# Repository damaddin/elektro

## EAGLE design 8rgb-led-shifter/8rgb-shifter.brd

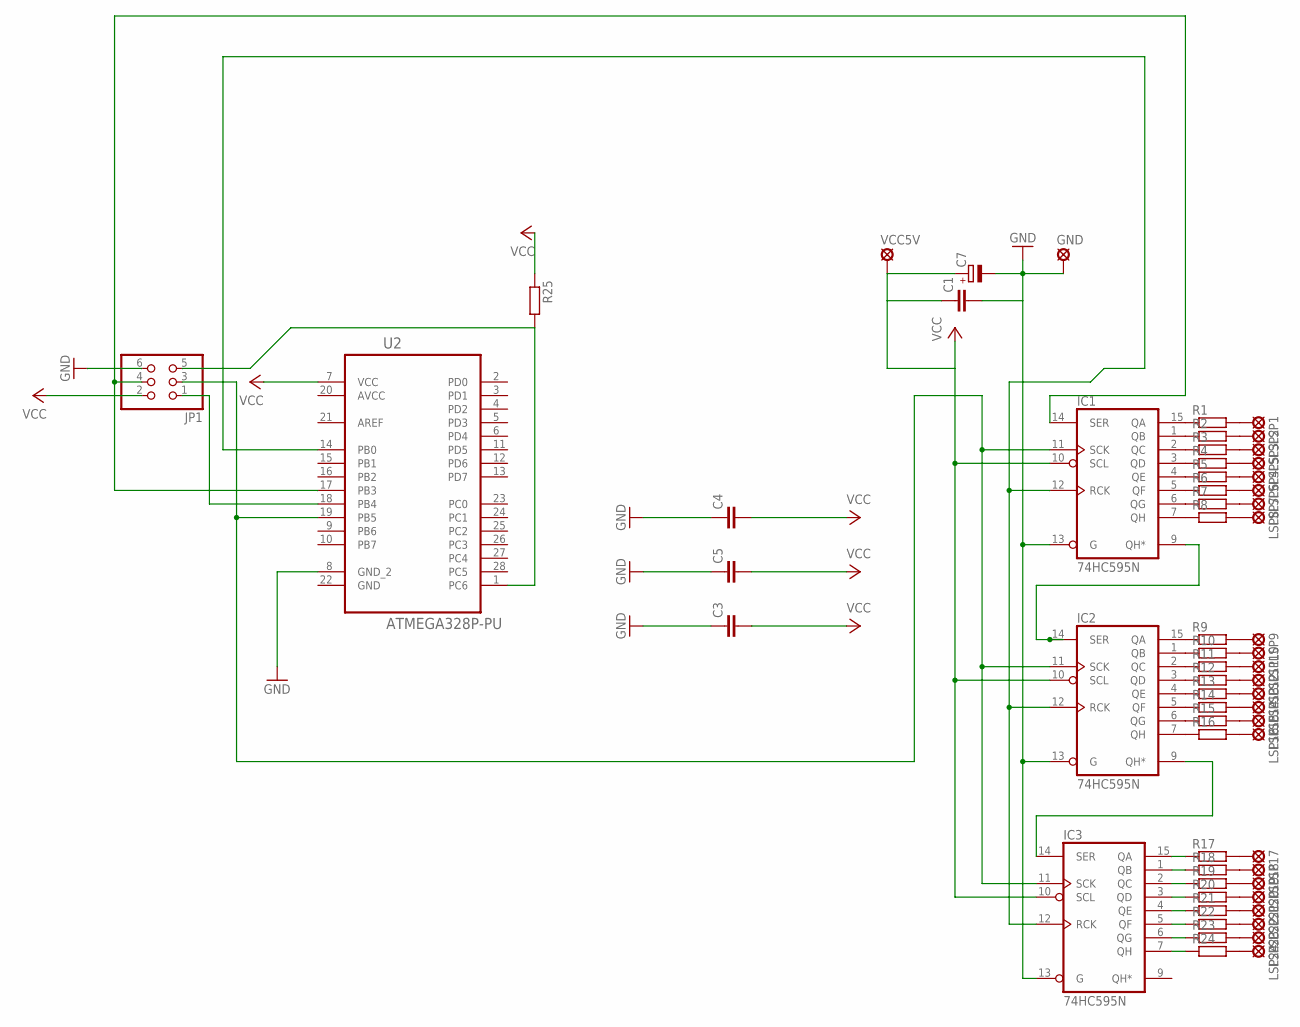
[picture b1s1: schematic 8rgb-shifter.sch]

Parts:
C1, C3, C4, C5: C-EU025-025X050; C025-025X050
C7: CPOL-EUE2,5-6E; E2,5-6E
GND: LSP10
IC1, IC2, IC3: 74HC595N; DIL16
JP1: PINHD-2X3; 2X03
LSP1, LSP2, LSP3, LSP4, LSP5, LSP6, LSP7, LSP8, LSP9, LSP10, LSP11, LSP12, LSP13, LSP14, LSP15, LSP16, LSP17, LSP18, LSP19, LSP20, LSP21, LSP22, LSP23, LSP24: LSP10
R1, R2, R3, R4, R5, R6, R7, R8, R9, R10, R11, R12, R13, R14, R15, R16, R17, R18, R19, R20, R21, R22, R23, R24: R-EU_0204/2V; 0204V
R25: R-EU_0204/7; 0204/7
U2: ATMEGA328P-PU; DIP254P762X457-28
VCC5V: LSP10

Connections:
AVCC: U2.20 (AVCC)
GND: C4.1, JP1.6, U2.8 (GND_2)
unnamed: JP1.1, U2.18 (PB4)
unnamed: IC1.11 (SCK), IC2.11 (SCK), IC3.11 (SCK), JP1.3, U2.19 (PB5)
unnamed: LSP1.MP, R1.2
unnamed: IC1.9 (QH*), IC2.14 (SER)
unnamed: IC2.9 (QH*), IC3.14 (SER)
unnamed: LSP17.MP, R17.2
unnamed: JP1.5, R25.2, U2.1 (PC6)
unnamed: IC1.14 (SER), JP1.4, U2.17 (PB3)
unnamed: IC1.15 (QA), R1.1
unnamed: IC1.1 (QB), R2.1
unnamed: IC1.2 (QC), R3.1
unnamed: IC1.3 (QD), R4.1
unnamed: IC1.4 (QE), R5.1
unnamed: IC1.5 (QF), R6.1
unnamed: IC1.6 (QG), R7.1
unnamed: IC1.7 (QH), R8.1
unnamed: IC2.15 (QA), R9.1
unnamed: IC2.1 (QB), R10.1
unnamed: IC2.2 (QC), R11.1
unnamed: IC2.3 (QD), R12.1
unnamed: IC2.4 (QE), R13.1
unnamed: IC2.5 (QF), R14.1
unnamed: IC2.6 (QG), R15.1
unnamed: IC2.7 (QH), R16.1
unnamed: IC3.15 (QA), R17.1
unnamed: IC3.1 (QB), R18.1
unnamed: IC3.2 (QC), R19.1
unnamed: IC3.3 (QD), R20.1
unnamed: IC3.4 (QE), R21.1
unnamed: IC3.5 (QF), R22.1
unnamed: IC3.6 (QG), R23.1
unnamed: IC3.7 (QH), R24.1
unnamed: LSP2.MP, R2.2
unnamed: LSP3.MP, R3.2
unnamed: LSP4.MP, R5.2
unnamed: LSP5.MP, R4.2
unnamed: LSP6.MP, R6.2
unnamed: LSP7.MP, R7.2
unnamed: LSP8.MP, R8.2
unnamed: LSP9.MP, R9.2
unnamed: LSP10.MP, R10.2
unnamed: LSP12.MP, R12.2
unnamed: LSP13.MP, R13.2
unnamed: LSP14.MP, R14.2
unnamed: LSP15.MP, R15.2
unnamed: LSP11.MP, R11.2
unnamed: LSP16.MP, R16.2
unnamed: LSP18.MP, R18.2
unnamed: LSP19.MP, R19.2
unnamed: LSP20.MP, R20.2
unnamed: LSP21.MP, R21.2
unnamed: LSP23.MP, R23.2
unnamed: LSP24.MP, R24.2
unnamed: LSP22.MP, R22.2
unnamed: C1.2, C3.1, C5.1, C7.-, GND.MP, IC1.8 (GND), IC1.13 (G), IC2.8 (GND), IC2.13 (G), IC3.8 (GND), IC3.13 (G)
unnamed: IC1.12 (RCK), IC2.12 (RCK), IC3.12 (RCK), U2.14 (PB0)
VCC: C1.1, C3.2, C4.2, C5.2, C7.+, IC1.10 (SCL), IC1.16 (VCC), IC2.10 (SCL), IC2.16 (VCC), IC3.10 (SCL), IC3.16 (VCC), JP1.2, R25.1, U2.7 (VCC), VCC5V.MP

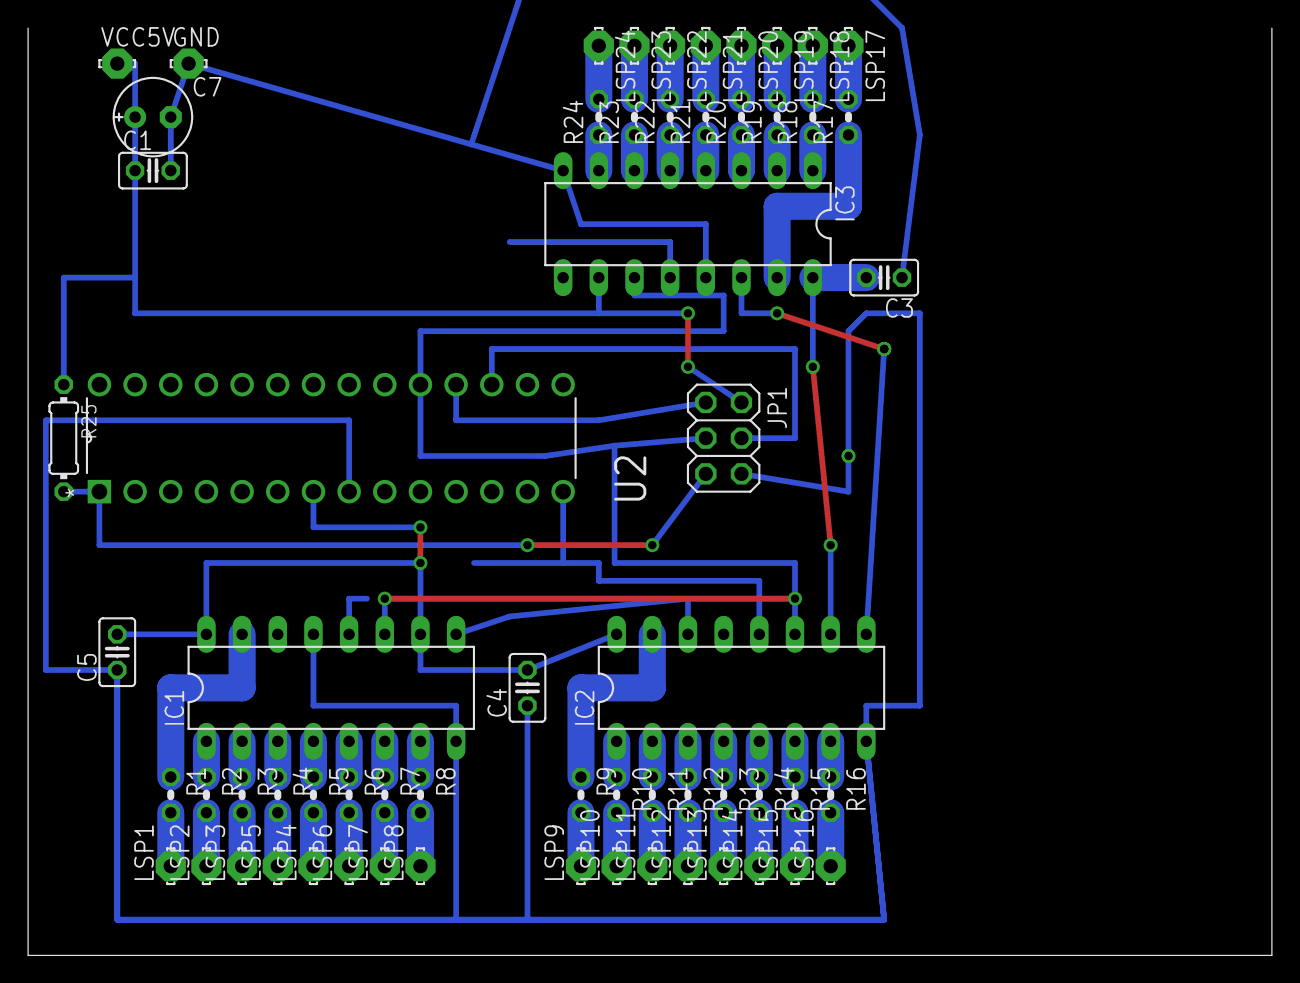
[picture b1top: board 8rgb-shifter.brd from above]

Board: 2 copper layers, 88.6 x 66.0 mm, 61 parts (0 on the bottom side), 58 nets.

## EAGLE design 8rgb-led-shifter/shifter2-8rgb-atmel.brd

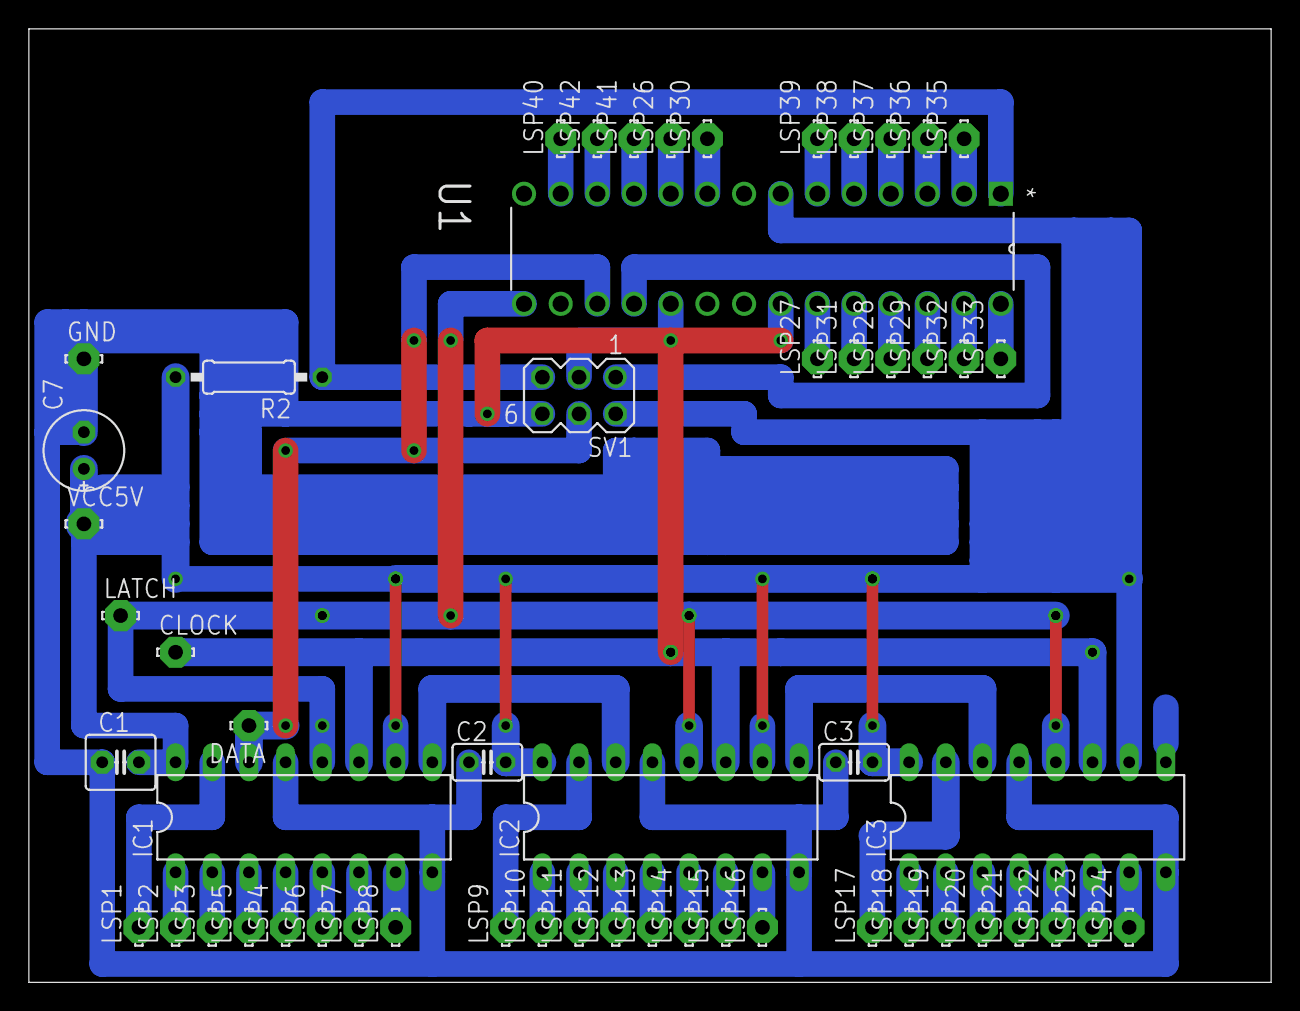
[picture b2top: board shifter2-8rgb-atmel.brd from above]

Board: 2 copper layers, 86.0 x 66.0 mm, 55 parts (0 on the bottom side), 50 nets.

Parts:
C1: C2.5-4
C2, C3: C025-025X050
C7: E2,5-6E
CLOCK: LSP10
DATA: LSP10
GND: LSP10
IC1, IC2, IC3: 74HC595N; DIL16
LATCH: LSP10
LSP1, LSP2, LSP3, LSP4, LSP5, LSP6, LSP7, LSP8, LSP9, LSP10, LSP11, LSP12, LSP13, LSP14, LSP15, LSP16, LSP17, LSP18, LSP19, LSP20, LSP21, LSP22, LSP23, LSP24, LSP26, LSP27, LSP28, LSP29, LSP30, LSP31, LSP32, LSP33, LSP35, LSP36, LSP37, LSP38, LSP39, LSP40, LSP41, LSP42: LSP10
R2: 0207/10
SV1: MA03-2
U1: ATMEGA168A-PU; DIP254P762X457-28
VCC5V: LSP10

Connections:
GND: SV1.6, U1.22
unnamed: IC2.15, LSP9.MP
unnamed: IC2.1, LSP10.MP
unnamed: IC2.2, LSP11.MP
unnamed: IC1.9, IC2.14
unnamed: IC2.9, IC3.14
unnamed: IC2.3, LSP12.MP
unnamed: IC2.4, LSP13.MP
unnamed: IC2.5, LSP14.MP
unnamed: IC2.6, LSP15.MP
unnamed: IC2.7, LSP16.MP
unnamed: IC1.15, LSP1.MP
unnamed: IC1.1, LSP2.MP
unnamed: IC1.2, LSP3.MP
unnamed: IC1.4, LSP4.MP
unnamed: IC1.3, LSP5.MP
unnamed: IC1.5, LSP6.MP
unnamed: IC1.6, LSP7.MP
unnamed: IC1.7, LSP8.MP
unnamed: R2.1, SV1.5, U1.1
unnamed: LSP28.MP, U1.25
unnamed: DATA.MP, IC1.14, SV1.4, U1.17
unnamed: SV1.1, U1.18
unnamed: LSP29.MP, U1.26
unnamed: LSP26.MP, U1.10
unnamed: LSP30.MP, U1.9
unnamed: IC3.15, LSP17.MP
unnamed: IC3.1, LSP18.MP
unnamed: IC3.2, LSP19.MP
unnamed: IC3.3, LSP20.MP
unnamed: IC3.4, LSP21.MP
unnamed: IC3.5, LSP22.MP
unnamed: IC3.6, LSP23.MP
unnamed: IC3.7, LSP24.MP
unnamed: LSP27.MP, U1.23
unnamed: LSP31.MP, U1.24
unnamed: LSP32.MP, U1.27
unnamed: LSP33.MP, U1.28
unnamed: LSP35.MP, U1.2
unnamed: LSP36.MP, U1.3
unnamed: LSP37.MP, U1.4
unnamed: LSP38.MP, U1.5
unnamed: LSP39.MP, U1.6
unnamed: LSP41.MP, U1.11
unnamed: LSP42.MP, U1.12
unnamed: LSP40.MP, U1.13
unnamed: CLOCK.MP, IC1.11, IC2.11, IC3.11, SV1.3, U1.19
unnamed: C1.1, C2.1, C3.1, C7.-, GND.MP, IC1.8, IC1.13, IC2.8, IC2.13, IC3.8, IC3.13
unnamed: IC1.12, IC2.12, IC3.12, LATCH.MP, U1.15
VCC: C1.2, C2.2, C3.2, C7.+, IC1.10, IC1.16, IC2.10, IC2.16, IC3.10, IC3.16, R2.2, SV1.2, U1.7, VCC5V.MP

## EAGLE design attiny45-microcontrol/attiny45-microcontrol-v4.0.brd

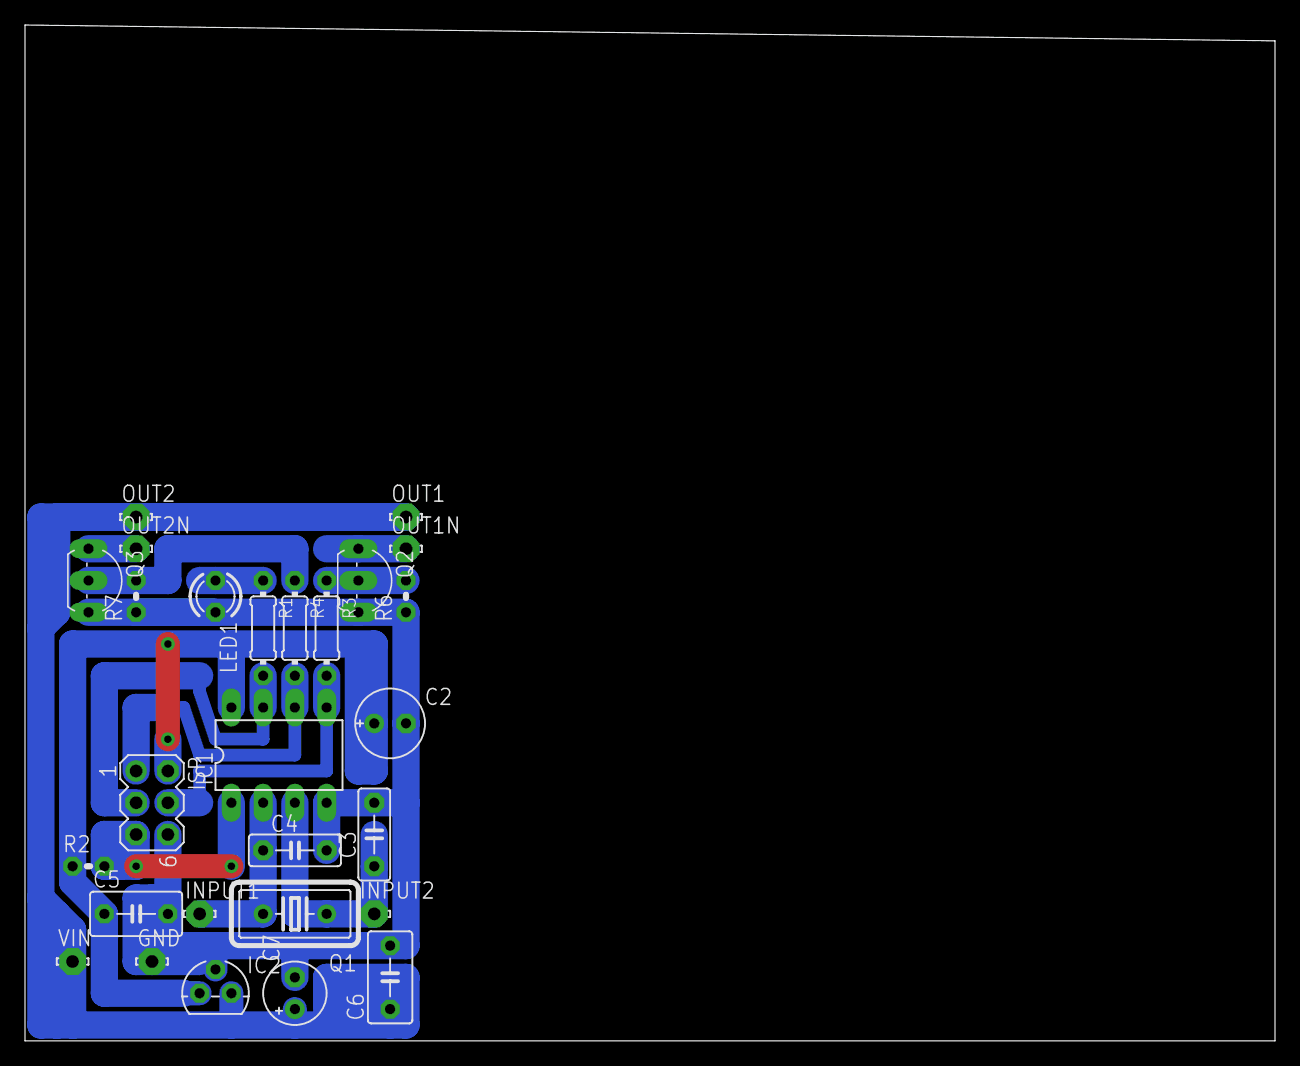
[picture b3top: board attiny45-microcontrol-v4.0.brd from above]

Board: 2 copper layers, 100.0 x 81.3 mm, 27 parts (0 on the bottom side), 14 nets.

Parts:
C2: 100u; E2,5-6E
C3, C4: 18nf; C5B2.5
C5, C6: 100n; C050-035X075
C7: 100y; E2,5-5
GND: LSP10
IC1: ATtiny13V; DIL08
IC2: 7805L; TO92
INPUT1, INPUT2: LSP10
ISP: isp 1; MA03-2
LED1: ROT; LED3MM
OUT1, OUT1N, OUT2, OUT2N: LSP10
Q1: 8mhz; HC18U-V
Q2, Q3: BC548; TO92-EBC
R1: 390; 0204/7
R2, R6, R7: 10k; 0204V
R3, R4: 1k; 0204/7
VIN: LSP10

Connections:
GND: C2.-, C3.2, C4.2, C5.2, C6.2, C7.-, GND.MP, IC1.4, IC2.2, ISP.6, LED1.K, Q2.E, Q3.E, R6.1, R7.1
unnamed: Q2.B, R3.1, R6.2
unnamed: C4.1, IC1.2, INPUT1.MP, Q1.2
unnamed: IC1.1, ISP.5, R2.2
unnamed: Q3.B, R4.1, R7.2
unnamed: IC1.7, ISP.3, R1.2
unnamed: IC1.6, ISP.1, R4.2
unnamed: LED1.A, R1.1
unnamed: C3.1, IC1.3, INPUT2.MP, Q1.1
unnamed: IC1.5, ISP.4, R3.2
unnamed: OUT2N.MP, Q3.C
unnamed: OUT1N.MP, Q2.C
unnamed: C6.1, C7.+, IC2.3, OUT1.MP, OUT2.MP, VIN.MP
VCC: C2.+, C5.1, IC1.8, IC2.1, ISP.2, R2.1

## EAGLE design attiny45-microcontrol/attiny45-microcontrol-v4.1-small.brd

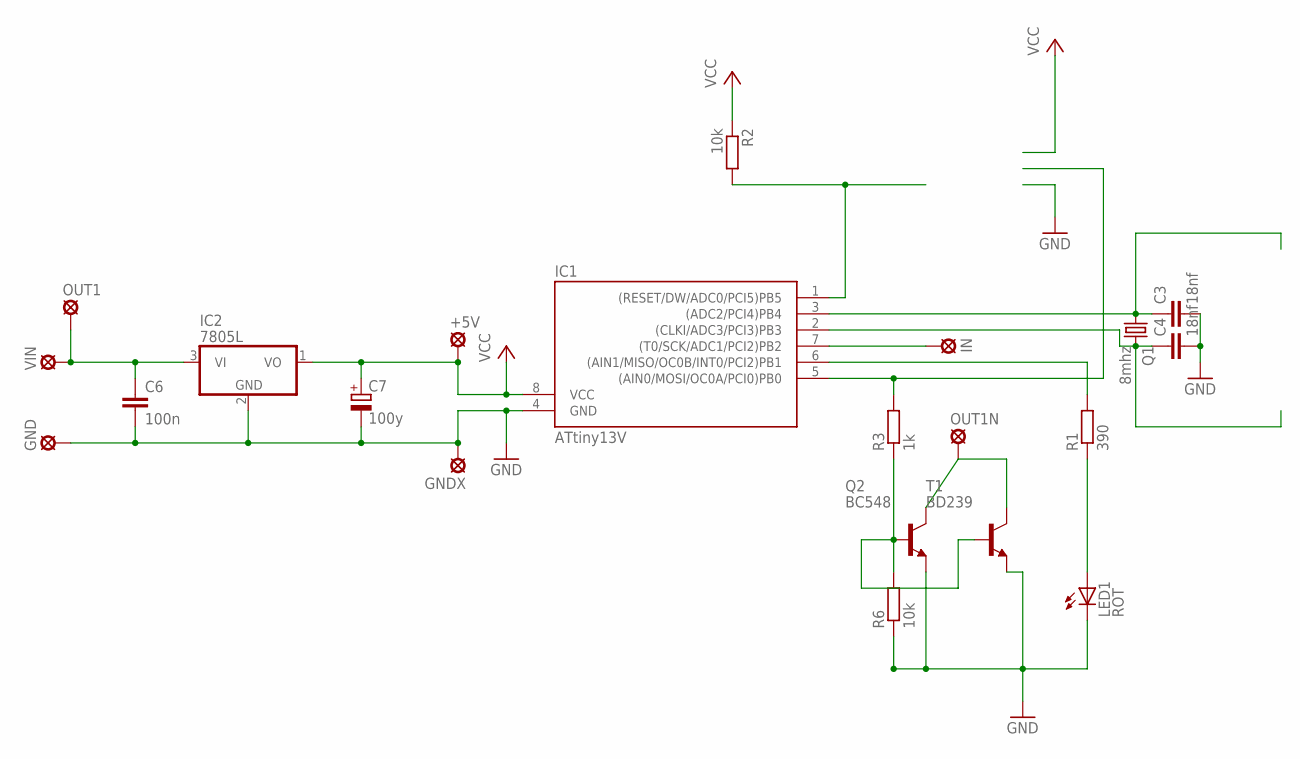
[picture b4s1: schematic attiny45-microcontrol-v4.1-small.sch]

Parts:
+5V: LSP10
C3, C4: 18nf; C5B2.5
C6: 100n; C050-035X075
C7: 100y; E2,5-5
GND: LSP10
GNDX: LSP10
IC1: ATtiny13V; DIL08
IC2: 7805L; TO92
IN: LSP10
LED1: ROT; LED3MM
OUT1, OUT1N: LSP10
Q1: 8mhz; HC18U-V
Q2: BC548; TO92-EBC
R1: 390; 0204/7
R2, R6: 10k; R1206
R3: 1k; 0204/7
T1: BD239; TO220
VIN: LSP10

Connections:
GND: C3.2, C4.2, C6.2, C7.-, GND.MP, GNDX.MP, IC1.4 (GND), IC2.2 (GND), LED1.K (C), Q2.E, R6.1, T1.3 (E)
unnamed: Q2.B, R3.1, R6.2, T1.1 (B)
unnamed: C4.1, IC1.2 ((CLKI/ADC3/PCI3)PB3), Q1.2
unnamed: IC1.1 ((RESET/DW/ADC0/PCI5)PB5), R2.2
unnamed: IC1.7 ((T0/SCK/ADC1/PCI2)PB2), IN.MP
unnamed: IC1.6 ((AIN1/MISO/OC0B/INT0/PCI2)PB1), R1.2
unnamed: LED1.A, R1.1
unnamed: C3.1, IC1.3 ((ADC2/PCI4)PB4), Q1.1
unnamed: IC1.5 ((AIN0/MOSI/OC0A/PCI0)PB0), R3.2
unnamed: OUT1N.MP, Q2.C, T1.2 (C)
unnamed: C6.1, IC2.3 (VI), OUT1.MP, VIN.MP
VCC: +5V.MP, C7.+, IC1.8 (VCC), IC2.1 (VO), R2.1

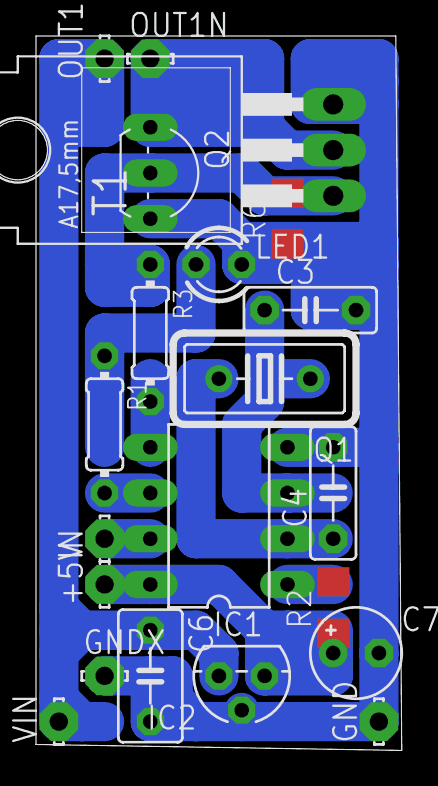
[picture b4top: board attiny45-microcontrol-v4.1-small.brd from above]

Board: 2 copper layers, 20.3 x 39.7 mm, 21 parts (0 on the bottom side), 12 nets.

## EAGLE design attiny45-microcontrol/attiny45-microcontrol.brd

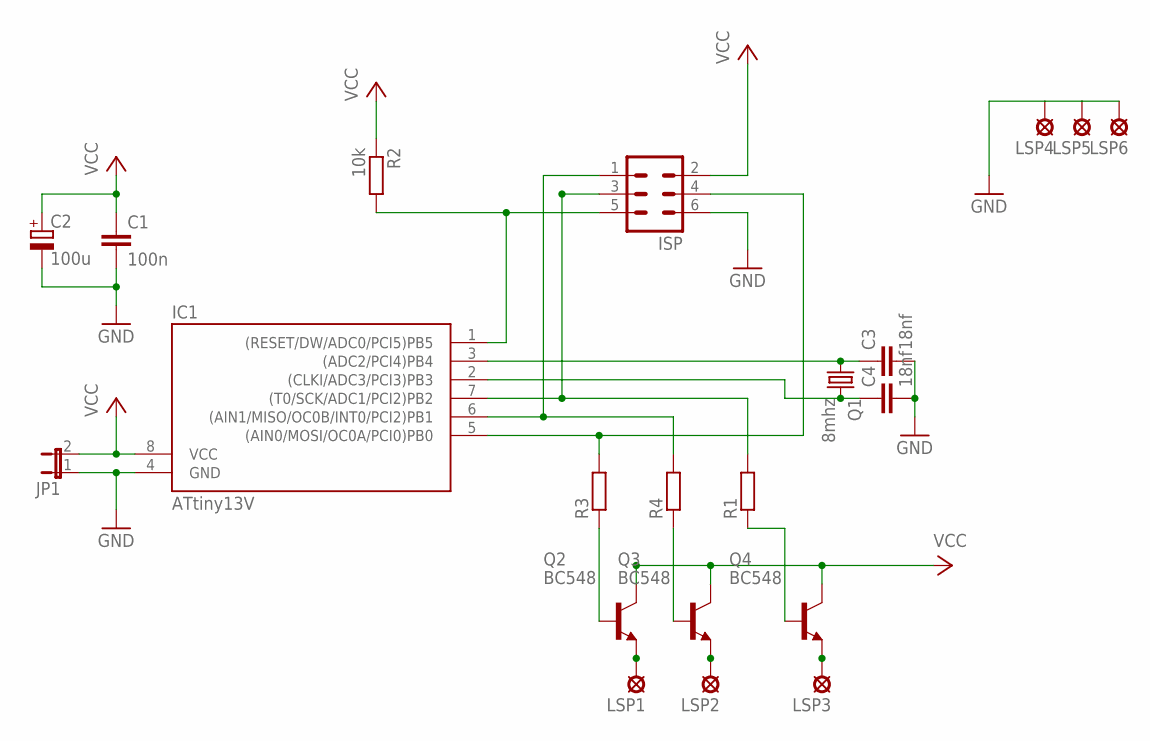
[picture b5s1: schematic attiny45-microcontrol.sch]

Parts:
C1: 100n; C025-025X050
C2: 100u; E2,5-6E
C3, C4: 18nf; C5B2.5
IC1: ATtiny13V; DIL08
ISP: MA03-2
JP1: JP1E; JP1
LSP1, LSP2, LSP3, LSP4, LSP5, LSP6: LSP10
Q1: 8mhz; HC18U-V
Q2, Q3, Q4: BC548; TO92-EBC
R1, R3, R4: R-EU_0204/5; 0204/5
R2: 10k; 0204/7

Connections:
GND: C1.2, C2.-, C3.2, C4.2, IC1.4 (GND), ISP.6, JP1.1, LSP4.MP, LSP5.MP, LSP6.MP
unnamed: Q2.B, R3.1
unnamed: C4.1, IC1.2 ((CLKI/ADC3/PCI3)PB3), Q1.2
unnamed: IC1.1 ((RESET/DW/ADC0/PCI5)PB5), ISP.5, R2.2
unnamed: Q3.B, R4.1
unnamed: IC1.7 ((T0/SCK/ADC1/PCI2)PB2), ISP.3, R1.2
unnamed: IC1.6 ((AIN1/MISO/OC0B/INT0/PCI2)PB1), ISP.1, R4.2
unnamed: Q4.B, R1.1
unnamed: C3.1, IC1.3 ((ADC2/PCI4)PB4), Q1.1
unnamed: IC1.5 ((AIN0/MOSI/OC0A/PCI0)PB0), ISP.4, R3.2
unnamed: LSP1.MP, Q2.E
unnamed: LSP2.MP, Q3.E
unnamed: LSP3.MP, Q4.E
VCC: C1.1, C2.+, IC1.8 (VCC), ISP.2, JP1.2, Q2.C, Q3.C, Q4.C, R2.1

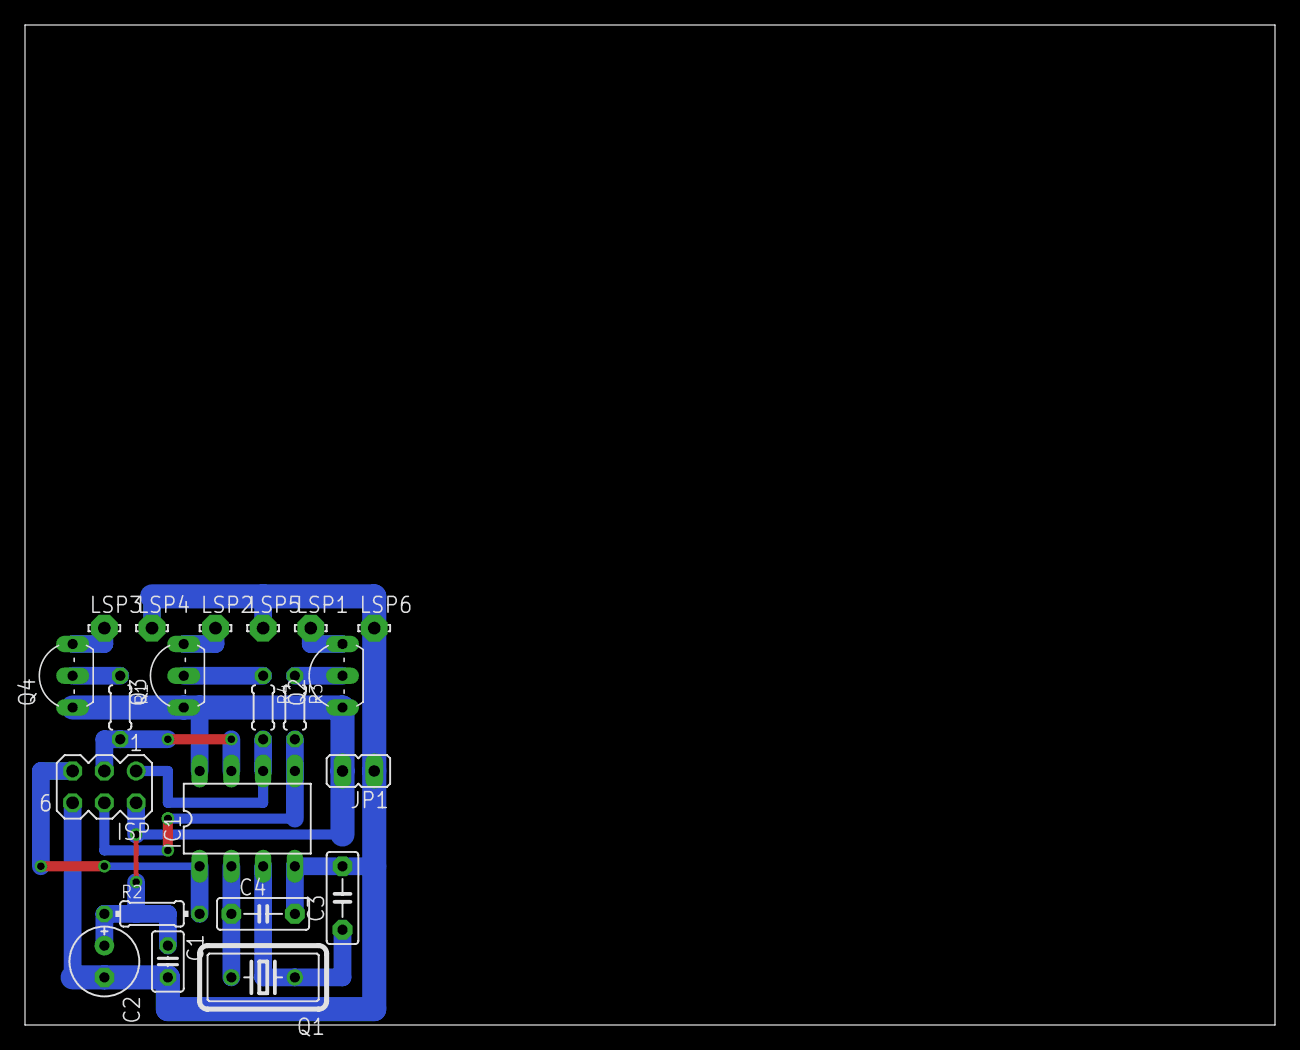
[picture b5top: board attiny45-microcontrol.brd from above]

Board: 2 copper layers, 100.0 x 80.0 mm, 21 parts (0 on the bottom side), 14 nets.

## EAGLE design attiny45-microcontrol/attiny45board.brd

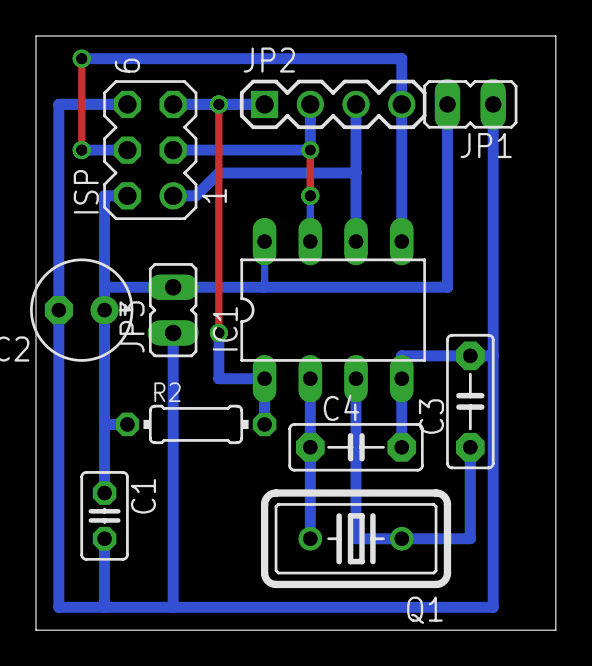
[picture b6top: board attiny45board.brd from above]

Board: 2 copper layers, 28.9 x 33.0 mm, 11 parts (0 on the bottom side), 8 nets.

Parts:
C1: 100n; C025-025X050
C2: 100u; E2,5-6E
C3, C4: 18nf; C5B2.5
IC1: ATtiny13V; DIL08
ISP: MA03-2
JP1, JP3: JP1
JP2: 1X04
Q1: 8mhz; HC18U-V
R2: 10k; 0204/7

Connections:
GND: C1.2, C2.-, C3.2, C4.2, IC1.4, ISP.6, JP1.1, JP3.1
unnamed: C4.1, IC1.2, Q1.2
unnamed: IC1.1, ISP.5, JP2.1, R2.2
unnamed: IC1.7, ISP.3, JP2.2
unnamed: IC1.6, ISP.1, JP2.3
unnamed: C3.1, IC1.3, Q1.1
unnamed: IC1.5, ISP.4, JP2.4
VCC: C1.1, C2.+, IC1.8, ISP.2, JP1.2, JP3.2, R2.1

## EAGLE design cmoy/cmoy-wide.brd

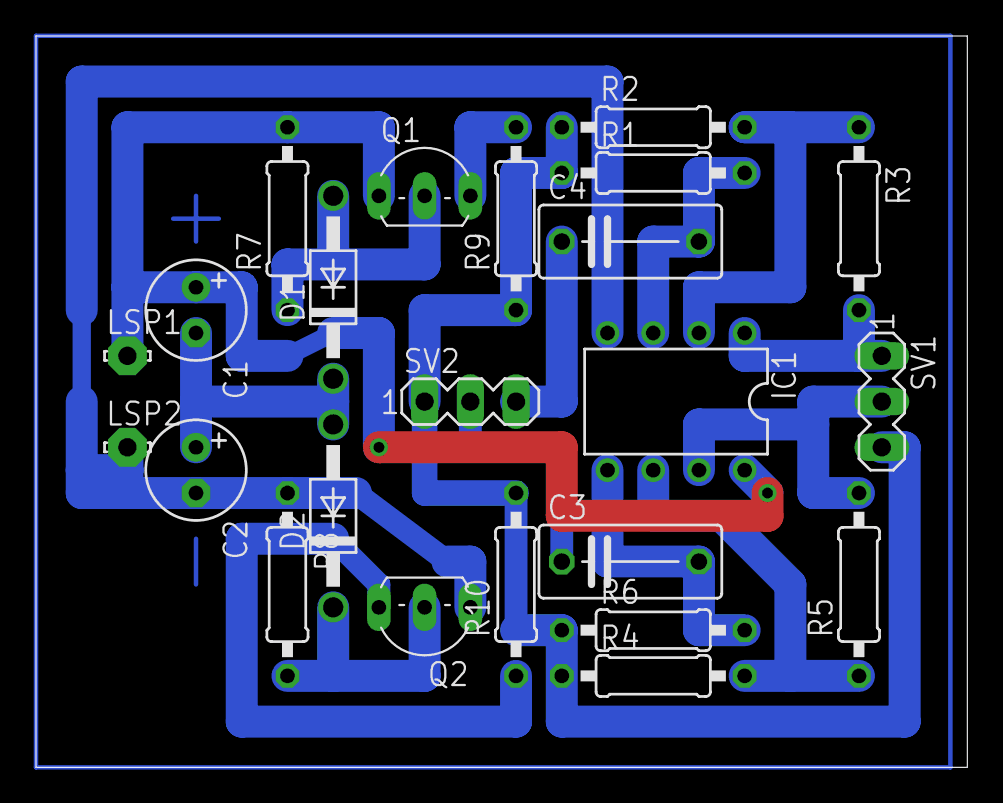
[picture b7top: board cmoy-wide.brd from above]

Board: 2 copper layers, 51.7 x 40.6 mm, 23 parts (0 on the bottom side), 16 nets.

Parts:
C1, C2: 220u; E2,5-6
C3, C4: 0.1u; C075-042X103
D1, D2: 1N4004; DO41-10
IC1: TL072P; DIL08
LSP1, LSP2: LSP10
Q1: BC548; TO92-EBC
Q2: BC556; TO92-EBC
R1, R6: 100k; 0207/10
R2, R4: 1k; 0207/10
R3, R5: 10k; 0207/10
R7, R8: 4.7k; 0207/10
R9, R10: 10; 0207/10
SV1, SV2: MA03-1

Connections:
GND: C2.-, IC1.4, LSP2.MP, Q2.C, R8.1
unnamed: C1.-, C2.+, D1.C, D2.A
unnamed: D2.C, Q2.B, R8.2
unnamed: D1.A, Q1.B, R7.1
unnamed: R1.1, R2.1, R4.1, R6.1, R9.1, R10.2, SV1.3, SV2.1
unnamed: Q1.E, R9.2
unnamed: Q2.E, R10.1
unnamed: IC1.2, R2.2, R3.1
unnamed: IC1.1, R3.2, SV1.1
unnamed: C4.2, IC1.3, R1.2
unnamed: C4.1, SV2.3
unnamed: IC1.7, R5.2, SV1.2
unnamed: IC1.6, R4.2, R5.1
unnamed: C3.2, IC1.5, R6.2
unnamed: C3.1, SV2.2
VCC: C1.+, IC1.8, LSP1.MP, Q1.C, R7.2
